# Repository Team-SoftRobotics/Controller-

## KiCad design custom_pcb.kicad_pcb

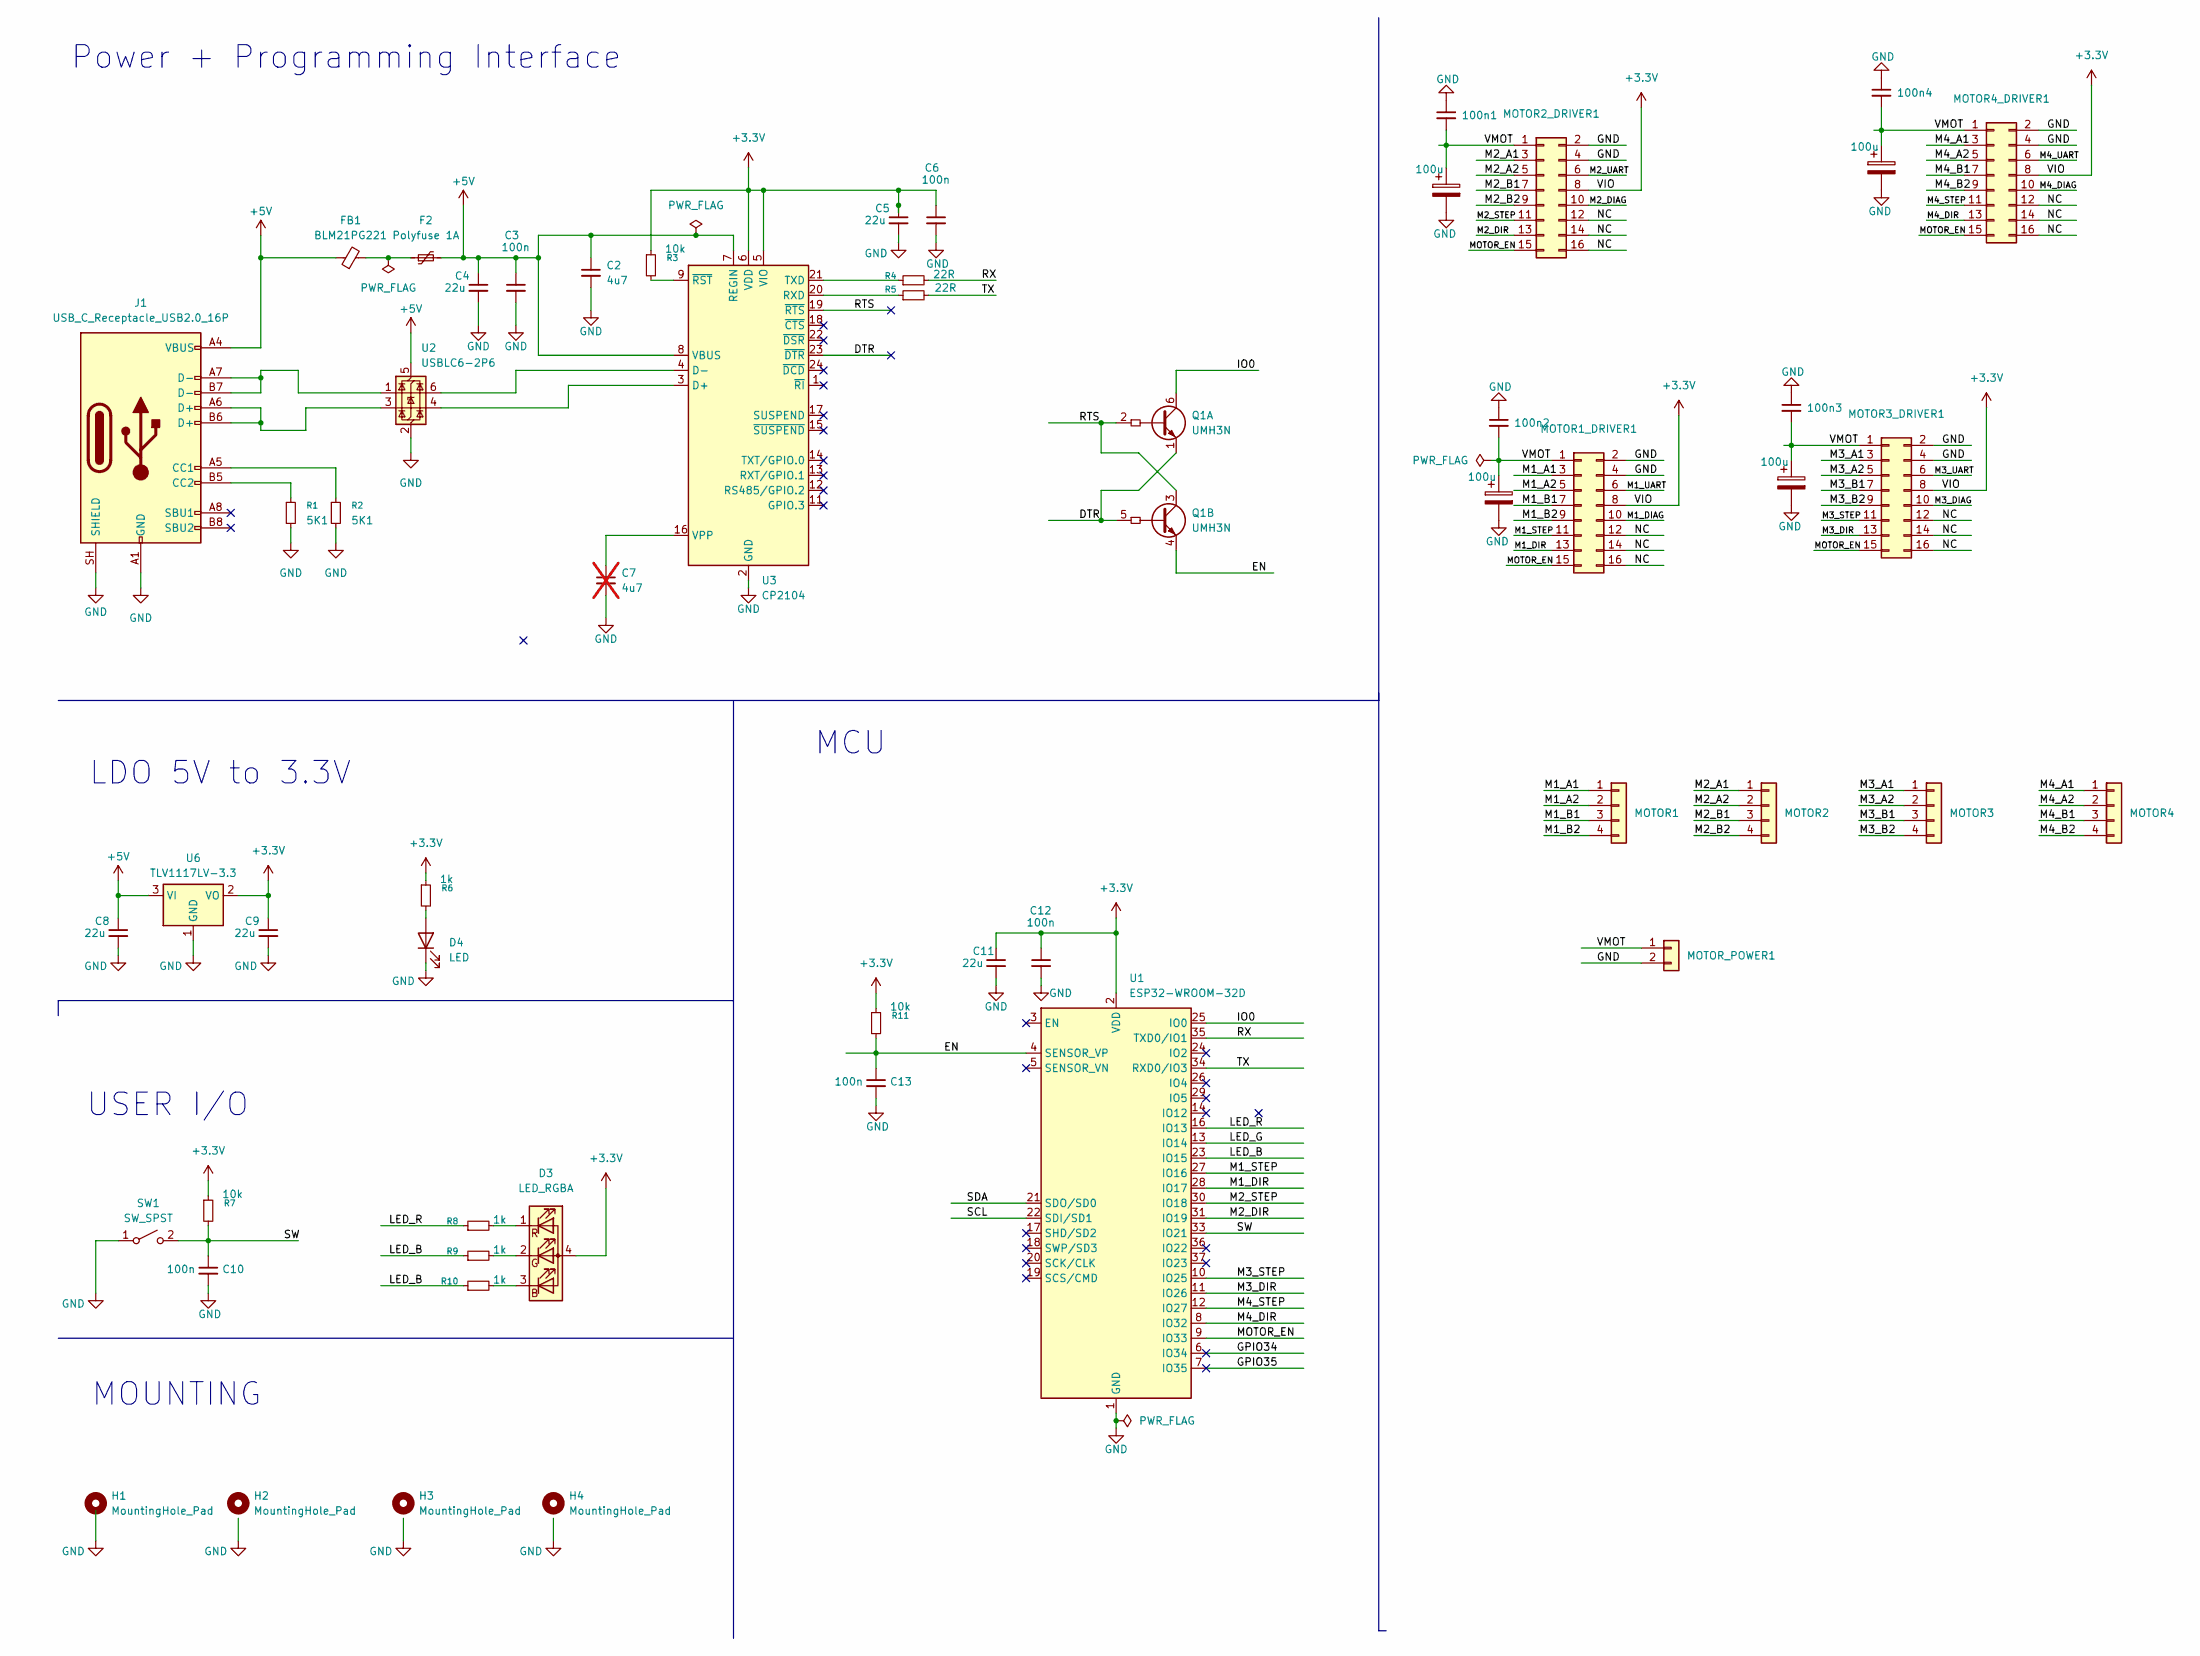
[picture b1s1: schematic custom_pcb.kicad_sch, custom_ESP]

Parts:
100n1, 100n2, 100n3, 100n4: C_Small; C_0603_1608Metric
C1, C14, C15, C16: 100u; CP_Elec_6.3x5.4
C2: 4u7; C_0805_2012Metric
C3, C6, C10, C12, C13: 100n; C_0603_1608Metric
C4, C5, C8, C9, C11: 22u; C_1206_3216Metric
C7: 4u7; C_0805_2012Metric; not fitted
D3: LED_RGBA; LED_RGB_1210
D4: LED; LED_0603_1608Metric
F2: Polyfuse 1A; Fuse_1812_4532Metric
FB1: BLM21PG221; R_0603_1608Metric
H1, H2, H3, H4: MountingHole_Pad; MountingHole_3.2mm_M3
J1: USB_C_Receptacle_USB2.0_16P; USB_C_Receptacle_GCT_USB4105-xx-A_16P_TopMnt_Horizontal
MOTOR1, MOTOR2, MOTOR3, MOTOR4: Conn_01x04; PinHeader_1x04_P2.54mm_Vertical
MOTOR1_DRIVER1, MOTOR2_DRIVER1, MOTOR3_DRIVER1, MOTOR4_DRIVER1: Conn_02x08_Odd_Even; PinSocket_2x08_P2.54mm_Vertical_SMD
MOTOR_POWER1: Conn_01x02; PinHeader_1x02_P2.54mm_Vertical_SMD_Pin1Left
Q1: UMH3N; SOT-363_SC-70-6
R1, R2: 5K1; R_0603_1608Metric
R3, R7, R11: 10k; R_0603_1608Metric
R4, R5: 22R; R_0603_1608Metric
R6, R8, R9, R10: 1k; R_0603_1608Metric
SW1: SW_SPST; SW_SPST_EVQP7A
U1: ESP32-WROOM-32D
U2: USBLC6-2P6; SOT-666
U3: CP2104; QFN-24-1EP_4x4mm_P0.5mm_EP2.6x2.6mm
U6: TLV1117LV-3.3; SOT-223-3_TabPin2

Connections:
+3.3V: C5.1, C6.1, C9.1, C11.1, C12.1, D3.4 (A), MOTOR1_DRIVER1.8, MOTOR2_DRIVER1.8, MOTOR3_DRIVER1.8, MOTOR4_DRIVER1.8, R3.1, R6.1, R7.1, R11.1, U1.2 (VDD), U3.5 (VIO), U3.6 (VDD), U6.2 (VO)
+5V: C2.1, C3.1, C4.1, C8.1, F2.2, FB1.1, J1.A4 (VBUS), J1.A9 (VBUS), J1.B4 (VBUS), J1.B9 (VBUS), U2.5 (VBUS), U3.7 (REGIN), U3.8 (VBUS), U6.3 (VI)
/DTR: Q1.1 (E1), Q1.5 (B2), U3.23 (~DTR)
/EN: C13.1, Q1.4 (E2), R11.2, U1.4 (SENSOR_VP)
/GPIO34: U1.6 (IO34)
/GPIO35: U1.7 (IO35)
/IO0: Q1.6 (C1), U1.25 (IO0)
/LED_B: R9.1, R10.1, U1.23 (IO15)
/LED_G: U1.13 (IO14)
/LED_R: R8.1, U1.16 (IO13)
/M1_A1: MOTOR1.1, MOTOR1_DRIVER1.3
/M1_A2: MOTOR1.2, MOTOR1_DRIVER1.5
/M1_B1: MOTOR1.3, MOTOR1_DRIVER1.7
/M1_B2: MOTOR1.4, MOTOR1_DRIVER1.9
/M1_DIAG: MOTOR1_DRIVER1.10
/M1_DIR: MOTOR1_DRIVER1.13, U1.28 (IO17)
/M1_STEP: MOTOR1_DRIVER1.11, U1.27 (IO16)
/M1_UART: MOTOR1_DRIVER1.6
/M2_A1: MOTOR2.1, MOTOR2_DRIVER1.3
/M2_A2: MOTOR2.2, MOTOR2_DRIVER1.5
/M2_B1: MOTOR2.3, MOTOR2_DRIVER1.7
/M2_B2: MOTOR2.4, MOTOR2_DRIVER1.9
/M2_DIAG: MOTOR2_DRIVER1.10
/M2_DIR: MOTOR2_DRIVER1.13, U1.31 (IO19)
/M2_STEP: MOTOR2_DRIVER1.11, U1.30 (IO18)
/M2_UART: MOTOR2_DRIVER1.6
/M3_A1: MOTOR3.1, MOTOR3_DRIVER1.3
/M3_A2: MOTOR3.2, MOTOR3_DRIVER1.5
/M3_B1: MOTOR3.3, MOTOR3_DRIVER1.7
/M3_B2: MOTOR3.4, MOTOR3_DRIVER1.9
/M3_DIAG: MOTOR3_DRIVER1.10
/M3_DIR: MOTOR3_DRIVER1.13, U1.11 (IO26)
/M3_STEP: MOTOR3_DRIVER1.11, U1.10 (IO25)
/M3_UART: MOTOR3_DRIVER1.6
/M4_A1: MOTOR4.1, MOTOR4_DRIVER1.3
/M4_A2: MOTOR4.2, MOTOR4_DRIVER1.5
/M4_B1: MOTOR4.3, MOTOR4_DRIVER1.7
/M4_B2: MOTOR4.4, MOTOR4_DRIVER1.9
/M4_DIAG: MOTOR4_DRIVER1.10
/M4_DIR: MOTOR4_DRIVER1.13, U1.8 (IO32)
/M4_STEP: MOTOR4_DRIVER1.11, U1.12 (IO27)
/M4_UART: MOTOR4_DRIVER1.6
/MOTOR_EN: MOTOR1_DRIVER1.15, MOTOR2_DRIVER1.15, MOTOR3_DRIVER1.15, MOTOR4_DRIVER1.15, U1.9 (IO33)
/NC: MOTOR1_DRIVER1.12, MOTOR1_DRIVER1.14, MOTOR1_DRIVER1.16, MOTOR2_DRIVER1.12, MOTOR2_DRIVER1.14, MOTOR2_DRIVER1.16, MOTOR3_DRIVER1.12, MOTOR3_DRIVER1.14, MOTOR3_DRIVER1.16, MOTOR4_DRIVER1.12, MOTOR4_DRIVER1.14, MOTOR4_DRIVER1.16
/RTS: Q1.2 (B1), Q1.3 (C2), U3.19 (~RTS)
/RX: R4.2, U1.35 (TXD0/IO1)
/SCL: U1.22 (SDI/SD1)
/SDA: U1.21 (SDO/SD0)
/SW: C10.1, R7.2, SW1.2 (B), U1.33 (IO21)
/TX: R5.2, U1.34 (RXD0/IO3)
/VMOT: 100n1.2, 100n2.2, 100n3.2, 100n4.2, C1.1, C14.1, C15.1, C16.1, MOTOR1_DRIVER1.1, MOTOR2_DRIVER1.1, MOTOR3_DRIVER1.1, MOTOR4_DRIVER1.1, MOTOR_POWER1.1
GND: 100n1.1, 100n2.1, 100n3.1, 100n4.1, C1.2, C2.2, C3.2, C4.2, C5.2, C6.2, C7.2, C8.2, C9.2, C10.2, C11.2, C12.2, C13.2, C14.2, C15.2, C16.2, D4.1 (K), J1.A1 (GND), J1.A12 (GND), J1.B1 (GND), J1.B12 (GND), J1.SH (SHIELD), MOTOR1_DRIVER1.2, MOTOR1_DRIVER1.4, MOTOR2_DRIVER1.2, MOTOR2_DRIVER1.4, MOTOR3_DRIVER1.2, MOTOR3_DRIVER1.4, MOTOR4_DRIVER1.2, MOTOR4_DRIVER1.4, MOTOR_POWER1.2, R1.2, R2.2, SW1.1 (A), U1.1 (GND), U1.15 (GND), U1.38 (GND), U1.39 (GND), U2.2 (GND), U3.2 (GND), U3.25 (GND), U6.1 (GND)
unnamed: D3.3 (BK), R10.2
unnamed: D3.2 (GK), R9.2
unnamed: D3.1 (RK), R8.2
unnamed: D4.2 (A), R6.2
unnamed: F2.1, FB1.2
unnamed: J1.A5 (CC1), R2.1
unnamed: J1.B5 (CC2), R1.1
unnamed: J1.A6 (D+), J1.B6 (D+), U2.3 (I/O2)
unnamed: J1.A7 (D-), J1.B7 (D-), U2.1 (I/O1)
unnamed: U2.4 (I/O2), U3.3 (D+)
unnamed: U2.6 (I/O1), U3.4 (D-)
unnamed: R5.1, U3.20 (RXD)
unnamed: R4.1, U3.21 (TXD)
unnamed: C7.1, U3.16 (VPP)
unnamed: R3.2, U3.9 (~RST)

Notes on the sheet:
USER I/O
Power + Programming Interface
MCU
LDO 5V to 3.3V
MOUNTING

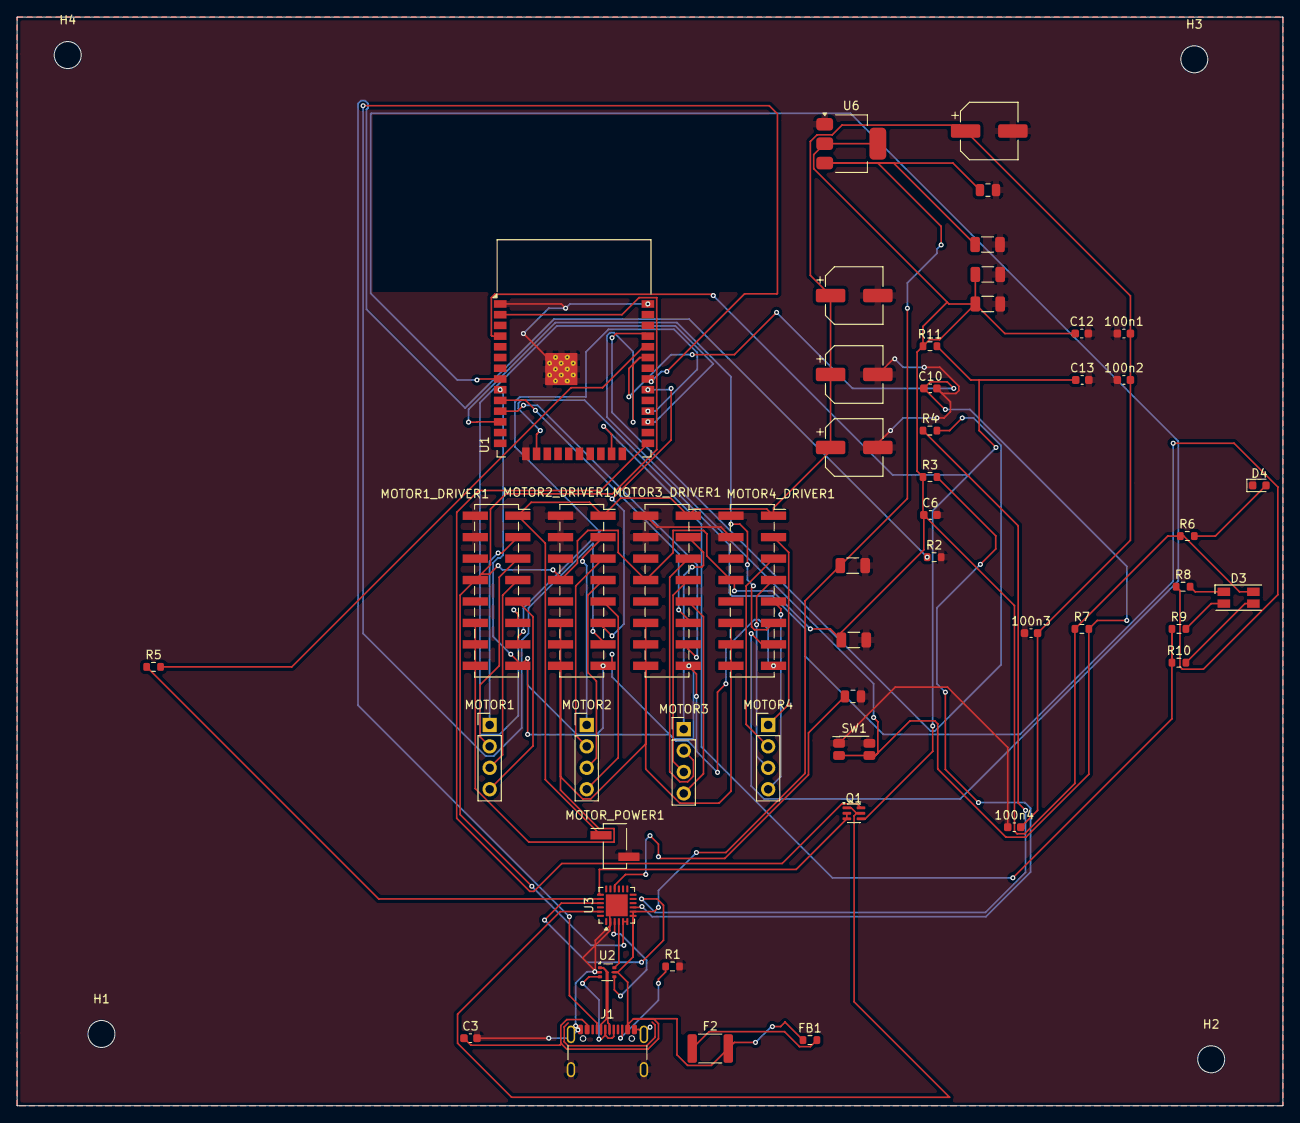
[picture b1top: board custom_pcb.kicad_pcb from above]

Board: 2 copper layers, 150.0 x 129.0 mm, 55 parts (0 on the bottom side), 54 nets.
